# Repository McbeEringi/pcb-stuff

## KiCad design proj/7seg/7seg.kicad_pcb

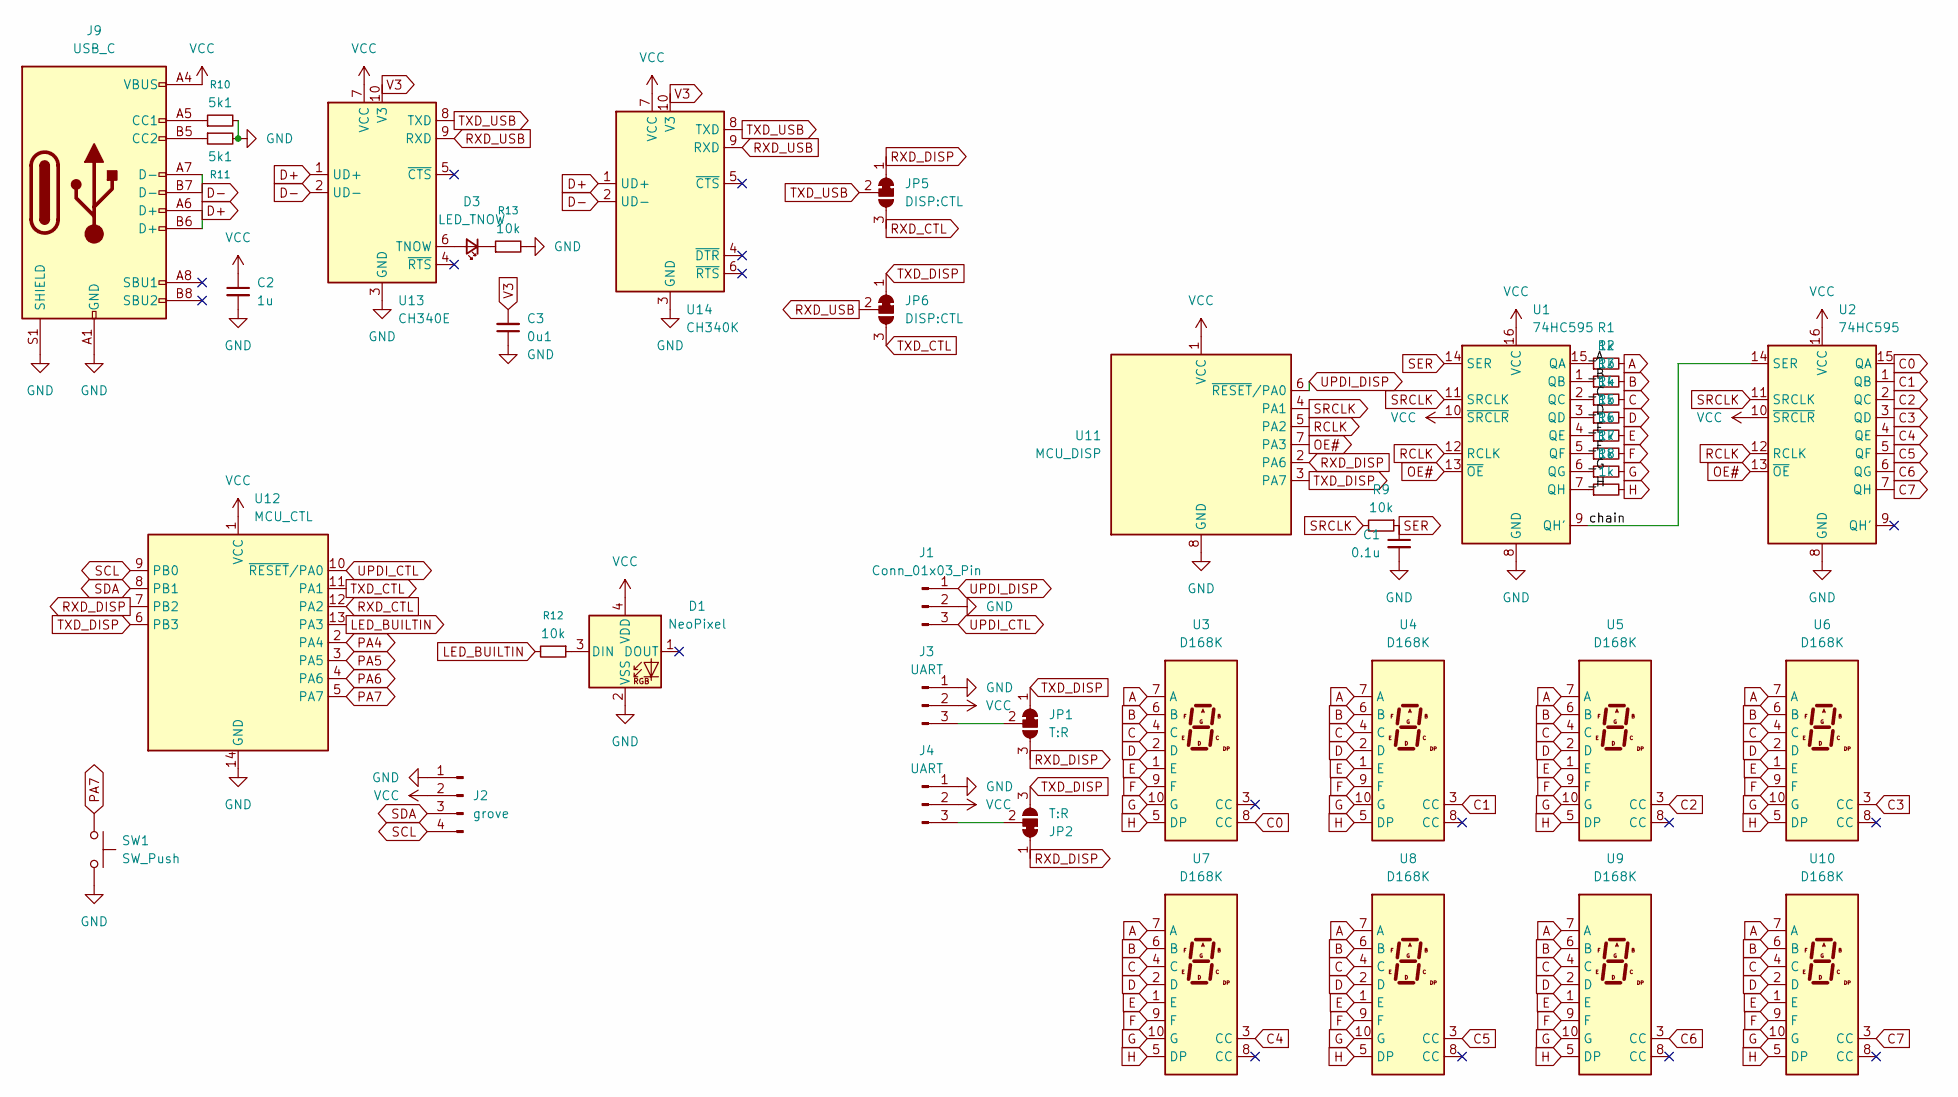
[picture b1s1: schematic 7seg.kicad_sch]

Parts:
C1: 0.1u; C_0603_1608Metric
C2: 1u; C_0603_1608Metric
C3: 0u1; C_0603_1608Metric
D1: NeoPixel; LED_WS2812B-2020_PLCC4_2.0x2.0mm
D3: LED_TNOW; LED_0603_1608Metric
J1: Conn_01x03_Pin; PinHeader_1x03_P2.54mm_Vertical
J2: grove; PinHeader_1x04_P2.54mm_Vertical
J3, J4: UART; PinHeader_1x03_P2.54mm_Vertical
J9: USB_C; USB_C_Receptacle_GCT_USB4105-xx-A_16P_TopMnt_Horizontal
JP1, JP2: T:R; SolderJumper-3_P1.3mm_Bridged12_RoundedPad1.0x1.5mm
JP5, JP6: DISP:CTL; SolderJumper-3_P1.3mm_Bridged12_RoundedPad1.0x1.5mm
R1, R2, R3, R4, R5, R6, R7, R8: 1k; R_0603_1608Metric
R9, R12, R13: 10k; R_0603_1608Metric
R10, R11: 5k1; R_0603_1608Metric
SW1: SW_Push; alps-skrp
U1, U2: 74HC595; TSSOP-16_4.4x5mm_P0.65mm
U3, U4, U5, U6, U7, U8, U9, U10: D168K; D1X8K
U11: MCU_DISP; SOIC-8_3.9x4.9mm_P1.27mm
U12: MCU_CTL; SOIC-14_3.9x8.7mm_P1.27mm
U13: CH340E; MSOP-10_3x3mm_P0.5mm
U14: CH340K; SSOP-10-1EP_3.9x4.9mm_P1mm_EP2.1x3.3mm

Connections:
/_A: R1.1, U1.15 (QA)
/_B: R2.1, U1.1 (QB)
/_C: R3.1, U1.2 (QC)
/_D: R4.1, U1.3 (QD)
/_E: R5.1, U1.4 (QE)
/_F: R6.1, U1.5 (QF)
/_G: R7.1, U1.6 (QG)
/_H: R8.1, U1.7 (QH)
/chain: U1.9 (QH'), U2.14 (SER)
A: R1.2, U3.7 (A), U4.7 (A), U5.7 (A), U6.7 (A), U7.7 (A), U8.7 (A), U9.7 (A), U10.7 (A)
B: R2.2, U3.6 (B), U4.6 (B), U5.6 (B), U6.6 (B), U7.6 (B), U8.6 (B), U9.6 (B), U10.6 (B)
C: R3.2, U3.4 (C), U4.4 (C), U5.4 (C), U6.4 (C), U7.4 (C), U8.4 (C), U9.4 (C), U10.4 (C)
C0: U2.15 (QA), U3.8 (CC)
C1: U2.1 (QB), U4.3 (CC)
C2: U2.2 (QC), U5.3 (CC)
C3: U2.3 (QD), U6.3 (CC)
C4: U2.4 (QE), U7.3 (CC)
C5: U2.5 (QF), U8.3 (CC)
C6: U2.6 (QG), U9.3 (CC)
C7: U2.7 (QH), U10.3 (CC)
D: R4.2, U3.2 (D), U4.2 (D), U5.2 (D), U6.2 (D), U7.2 (D), U8.2 (D), U9.2 (D), U10.2 (D)
D+: J9.A6 (D+), J9.B6 (D+), U13.1 (UD+), U14.1 (UD+)
D-: J9.A7 (D-), J9.B7 (D-), U13.2 (UD-), U14.2 (UD-)
E: R5.2, U3.1 (E), U4.1 (E), U5.1 (E), U6.1 (E), U7.1 (E), U8.1 (E), U9.1 (E), U10.1 (E)
F: R6.2, U3.9 (F), U4.9 (F), U5.9 (F), U6.9 (F), U7.9 (F), U8.9 (F), U9.9 (F), U10.9 (F)
G: R7.2, U3.10 (G), U4.10 (G), U5.10 (G), U6.10 (G), U7.10 (G), U8.10 (G), U9.10 (G), U10.10 (G)
GND: C1.2, C2.2, C3.1, D1.2 (VSS), J1.2, J2.1, J3.1, J4.1, J9.A1 (GND), J9.A12 (GND), J9.B1 (GND), J9.B12 (GND), J9.S1 (SHIELD), R10.2, R11.2, R13.2, SW1.2, U1.8 (GND), U2.8 (GND), U11.8 (GND), U12.14 (GND), U13.3 (GND), U14.3 (GND)
H: R8.2, U3.5 (DP), U4.5 (DP), U5.5 (DP), U6.5 (DP), U7.5 (DP), U8.5 (DP), U9.5 (DP), U10.5 (DP)
LED_BUILTIN: R12.2, U12.13 (PA3)
unnamed: D1.3 (DIN), R12.1
unnamed: D3.2 (A), U13.6 (TNOW)
unnamed: D3.1 (K), R13.1
unnamed: J3.3, JP1.2 (C)
unnamed: J4.3, JP2.2 (C)
unnamed: J9.A5 (CC1), R10.1
unnamed: J9.B5 (CC2), R11.1
OE#: U1.13 (~OE), U2.13 (~OE), U11.7 (PA3)
PA4: U12.2 (PA4)
PA5: U12.3 (PA5)
PA6: U12.4 (PA6)
PA7: SW1.1, U12.5 (PA7)
RCLK: U1.12 (RCLK), U2.12 (RCLK), U11.5 (PA2)
RXD_CTL: JP5.3 (B), U12.12 (PA2)
RXD_DISP: JP1.3 (B), JP2.1 (A), JP5.1 (A), U11.2 (PA6), U12.7 (PB2)
RXD_USB: JP6.2 (C), U13.9 (RXD), U14.9 (RXD)
SCL: J2.4, U12.9 (PB0)
SDA: J2.3, U12.8 (PB1)
SER: C1.1, R9.1, U1.14 (SER)
SRCLK: R9.2, U1.11 (SRCLK), U2.11 (SRCLK), U11.4 (PA1)
TXD_CTL: JP6.3 (B), U12.11 (PA1)
TXD_DISP: JP1.1 (A), JP2.3 (B), JP6.1 (A), U11.3 (PA7), U12.6 (PB3)
TXD_USB: JP5.2 (C), U13.8 (TXD), U14.8 (TXD)
UPDI_CTL: J1.3, U12.10 (~RESET/PA0)
UPDI_DISP: J1.1, U11.6 (~RESET/PA0)
V3: C3.2, U13.10 (V3), U14.10 (V3)
VCC: C2.1, D1.4 (VDD), J2.2, J3.2, J4.2, J9.A4 (VBUS), J9.A9 (VBUS), J9.B4 (VBUS), J9.B9 (VBUS), U1.10 (~SRCLR), U1.16 (VCC), U2.10 (~SRCLR), U2.16 (VCC), U11.1 (VCC), U12.1 (VCC), U13.7 (VCC), U14.7 (VCC)

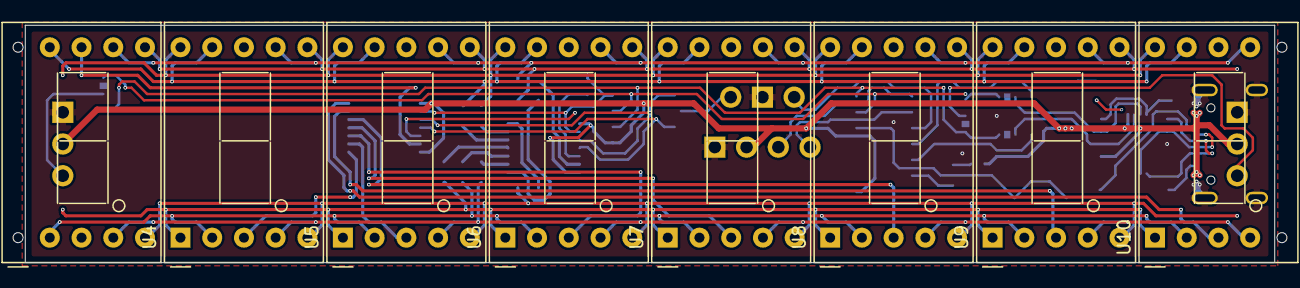
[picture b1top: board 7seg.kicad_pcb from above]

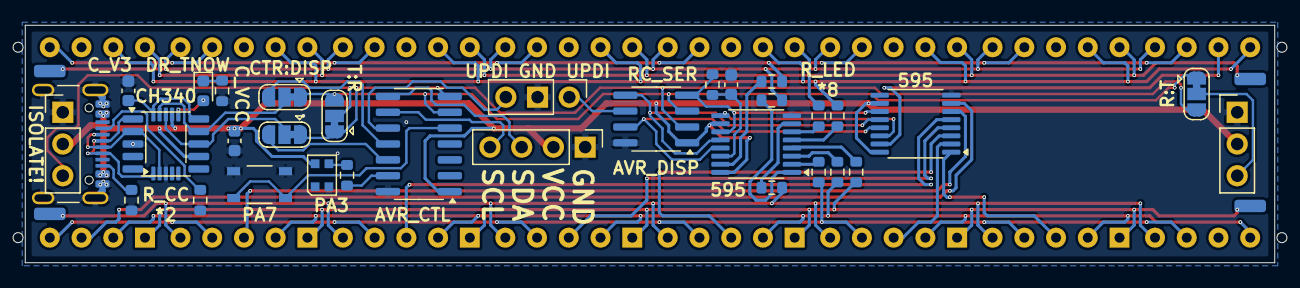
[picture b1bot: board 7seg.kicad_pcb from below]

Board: 2 copper layers, 100.0 x 19.0 mm, 42 parts (34 on the bottom side), 53 nets.

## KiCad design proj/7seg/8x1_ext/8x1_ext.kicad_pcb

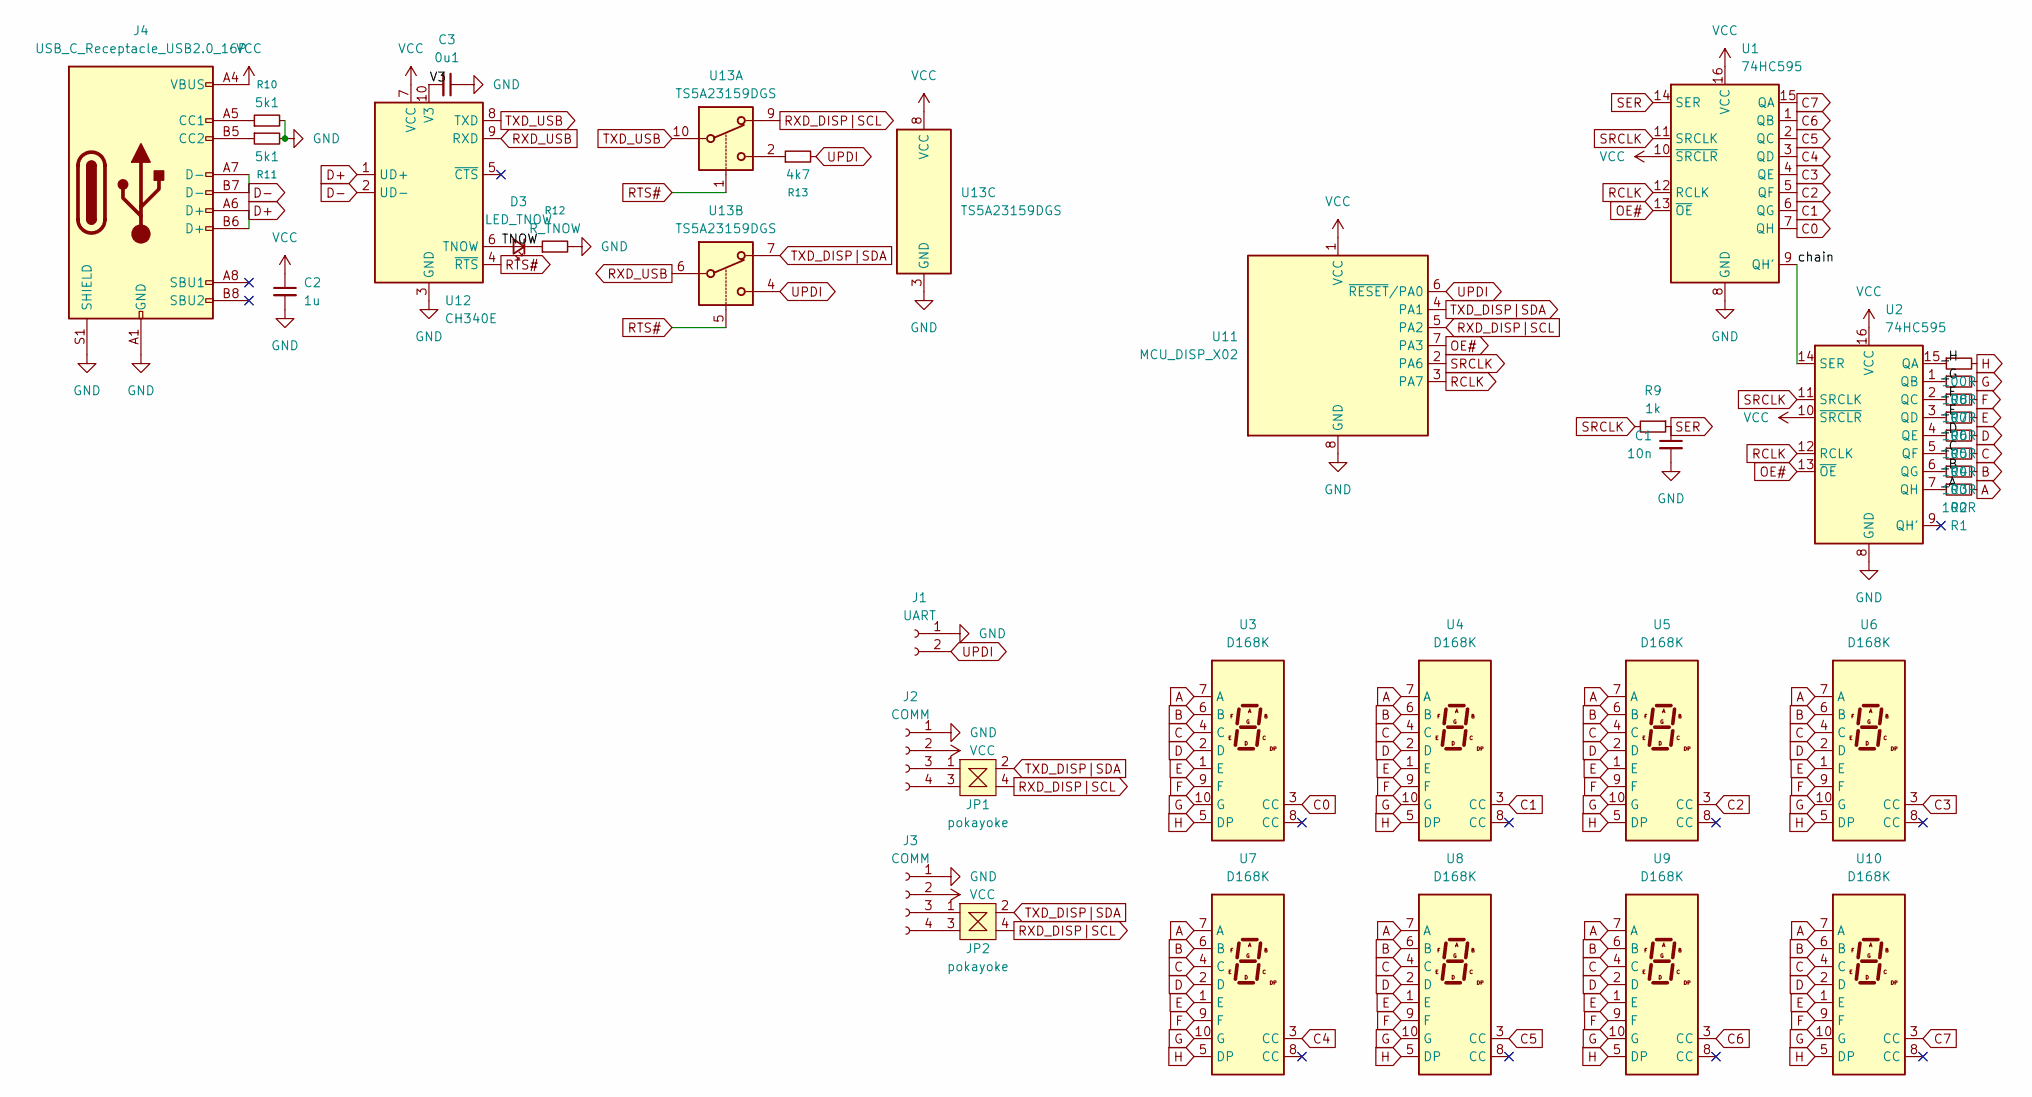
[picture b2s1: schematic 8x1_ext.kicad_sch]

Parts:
C1: 10n; C_0603_1608Metric
C2: 1u; C_0603_1608Metric
C3: 0u1; C_0603_1608Metric
D3: LED_TNOW; LED_0603_1608Metric
J1: UART; PinSocket_1x02_P2.54mm_Vertical
J2, J3: COMM; JST_ZH_B4B-ZR_1x04_P1.50mm_Vertical
J4: USB_C_Receptacle_USB2.0_16P; USB_C_Receptacle_GCT_USB4105-xx-A_16P_TopMnt_Horizontal
JP1, JP2: pokayoke; pokayoke_1608
R1, R2, R3, R4, R5, R6, R7, R8: 100R; R_0603_1608Metric
R9: 1k; R_0603_1608Metric
R10, R11: 5k1; R_0603_1608Metric
R12: R_TNOW; R_0603_1608Metric
R13: 4k7; R_0603_1608Metric
U1, U2: 74HC595; TSSOP-16_4.4x5mm_P0.65mm
U3, U4, U5, U6, U7, U8, U9, U10: D168K; D1X8K
U11: MCU_DISP_X02; SOIC-8_3.9x4.9mm_P1.27mm
U12: CH340E; MSOP-10_3x3mm_P0.5mm
U13: TS5A23159DGS; VSSOP-10_3x3mm_P0.5mm

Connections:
/TNOW: D3.2 (A), U12.6 (TNOW)
/V3: C3.2, U12.10 (V3)
/_A: R1.1, U2.7 (QH)
/_B: R2.1, U2.6 (QG)
/_C: R3.1, U2.5 (QF)
/_D: R4.1, U2.4 (QE)
/_E: R5.1, U2.3 (QD)
/_F: R6.1, U2.2 (QC)
/_G: R7.1, U2.1 (QB)
/_H: R8.1, U2.15 (QA)
/chain: U1.9 (QH'), U2.14 (SER)
A: R1.2, U3.7 (A), U4.7 (A), U5.7 (A), U6.7 (A), U7.7 (A), U8.7 (A), U9.7 (A), U10.7 (A)
B: R2.2, U3.6 (B), U4.6 (B), U5.6 (B), U6.6 (B), U7.6 (B), U8.6 (B), U9.6 (B), U10.6 (B)
C: R3.2, U3.4 (C), U4.4 (C), U5.4 (C), U6.4 (C), U7.4 (C), U8.4 (C), U9.4 (C), U10.4 (C)
C0: U1.7 (QH), U3.3 (CC)
C1: U1.6 (QG), U4.3 (CC)
C2: U1.5 (QF), U5.3 (CC)
C3: U1.4 (QE), U6.3 (CC)
C4: U1.3 (QD), U7.3 (CC)
C5: U1.2 (QC), U8.3 (CC)
C6: U1.1 (QB), U9.3 (CC)
C7: U1.15 (QA), U10.3 (CC)
D: R4.2, U3.2 (D), U4.2 (D), U5.2 (D), U6.2 (D), U7.2 (D), U8.2 (D), U9.2 (D), U10.2 (D)
D+: J4.A6 (D+), J4.B6 (D+), U12.1 (UD+)
D-: J4.A7 (D-), J4.B7 (D-), U12.2 (UD-)
E: R5.2, U3.1 (E), U4.1 (E), U5.1 (E), U6.1 (E), U7.1 (E), U8.1 (E), U9.1 (E), U10.1 (E)
F: R6.2, U3.9 (F), U4.9 (F), U5.9 (F), U6.9 (F), U7.9 (F), U8.9 (F), U9.9 (F), U10.9 (F)
G: R7.2, U3.10 (G), U4.10 (G), U5.10 (G), U6.10 (G), U7.10 (G), U8.10 (G), U9.10 (G), U10.10 (G)
GND: C1.2, C2.2, C3.1, J1.1, J2.1, J3.1, J4.A1 (GND), J4.A12 (GND), J4.B1 (GND), J4.B12 (GND), J4.S1 (SHIELD), R10.2, R11.2, R12.2, U1.8 (GND), U2.8 (GND), U11.8 (GND), U12.3 (GND), U13.3 (GND)
H: R8.2, U3.5 (DP), U4.5 (DP), U5.5 (DP), U6.5 (DP), U7.5 (DP), U8.5 (DP), U9.5 (DP), U10.5 (DP)
unnamed: D3.1 (K), R12.1
unnamed: J2.3, JP1.1
unnamed: J2.4, JP1.3
unnamed: J3.3, JP2.1
unnamed: J3.4, JP2.3
unnamed: J4.A5 (CC1), R10.1
unnamed: J4.B5 (CC2), R11.1
unnamed: R13.1, U13.2
OE#: U1.13 (~OE), U2.13 (~OE), U11.7 (PA3)
RCLK: U1.12 (RCLK), U2.12 (RCLK), U11.3 (PA7)
RTS#: U12.4 (~RTS), U13.1, U13.5
RXD_DISP|SCL: JP1.4, JP2.4, U11.5 (PA2), U13.9
RXD_USB: U12.9 (RXD), U13.6
SER: C1.1, R9.1, U1.14 (SER)
SRCLK: R9.2, U1.11 (SRCLK), U2.11 (SRCLK), U11.2 (PA6)
TXD_DISP|SDA: JP1.2, JP2.2, U11.4 (PA1), U13.7
TXD_USB: U12.8 (TXD), U13.10
UPDI: J1.2, R13.2, U11.6 (~RESET/PA0), U13.4
VCC: C2.1, J2.2, J3.2, J4.A4 (VBUS), J4.A9 (VBUS), J4.B4 (VBUS), J4.B9 (VBUS), U1.10 (~SRCLR), U1.16 (VCC), U2.10 (~SRCLR), U2.16 (VCC), U11.1 (VCC), U12.7 (VCC), U13.8 (VCC)

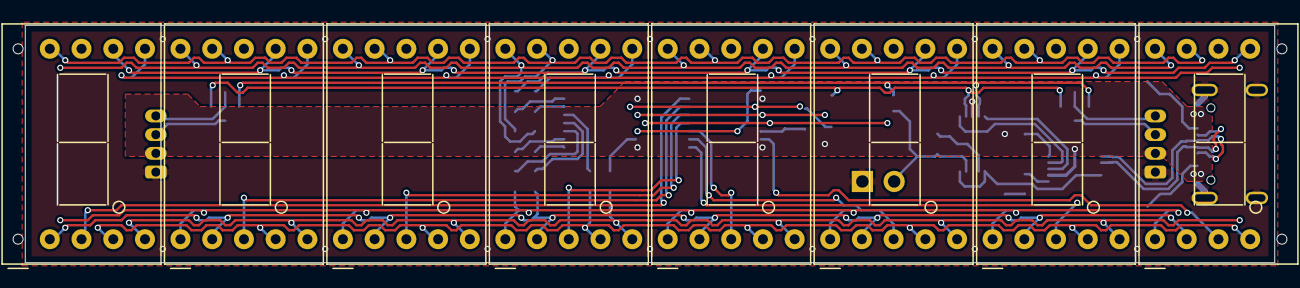
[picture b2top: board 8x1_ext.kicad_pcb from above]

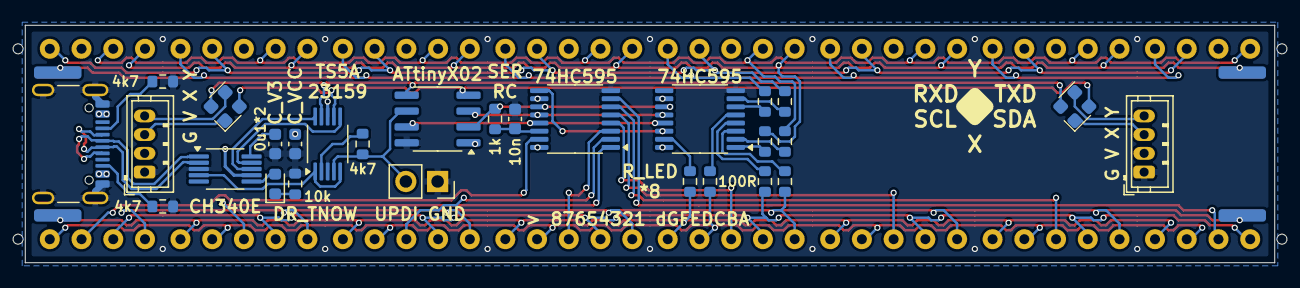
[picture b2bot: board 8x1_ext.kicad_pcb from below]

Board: 2 copper layers, 100.0 x 19.0 mm, 36 parts (28 on the bottom side), 49 nets.

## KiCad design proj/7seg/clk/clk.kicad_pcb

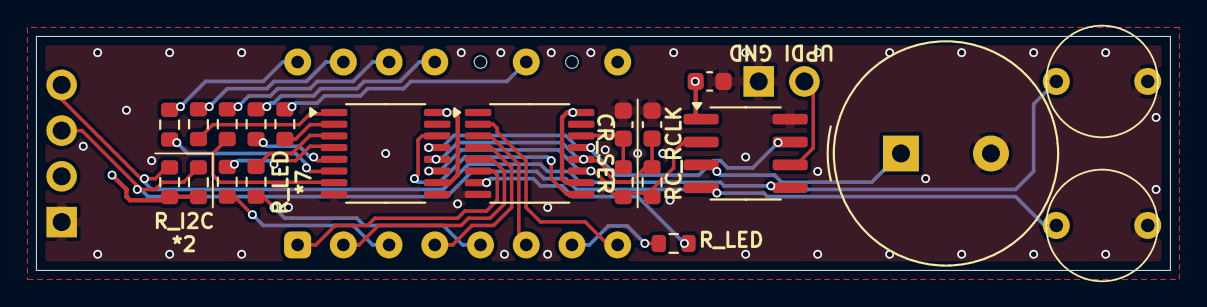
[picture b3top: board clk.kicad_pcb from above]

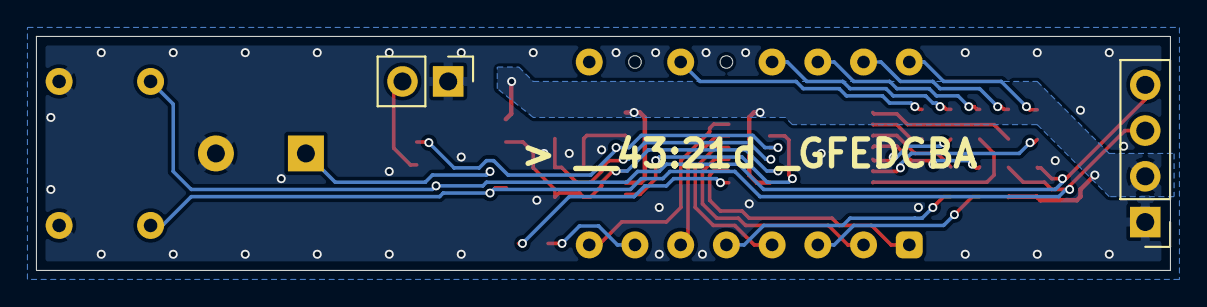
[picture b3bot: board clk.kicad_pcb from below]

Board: 2 copper layers, 63.0 x 13.0 mm, 24 parts (2 on the bottom side), 32 nets.

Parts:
BZ1: Buzzer; Buzzer_TDK_PS1240P02BT_D12.2mm_H6.5mm
C1: C_RCLK; C_0603_1608Metric
C2: C_SER; C_0603_1608Metric
C3: 1u; C_0603_1608Metric
J1: Conn_01x02_Pin; PinHeader_1x02_P2.54mm_Vertical
J2: Conn_01x04_Pin; PinHeader_1x04_P2.54mm_Vertical
R1, R2, R3, R4, R5, R6, R7, R8: 1k; R_0603_1608Metric
R9: R_RCLK; R_0603_1608Metric
R10: R_SER; R_0603_1608Metric
R11, R12: R_I2C; R_0603_1608Metric
SW1, SW2: SW_Push; alps-skrg
U1: LTC-4627JG; LTC-4627Jx
U2, U3: 74HC595; TSSOP-16_4.4x5mm_P0.65mm
U4: ATtiny402-SS; SOIC-8_3.9x4.9mm_P1.27mm

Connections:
/_SEG1: R1.1, U2.7 (QH)
/_SEG2: R2.1, U2.6 (QG)
/_SEG3: R3.1, U2.5 (QF)
/_SEG4: R4.1, U2.4 (QE)
/_SEG5: R5.1, U2.3 (QD)
/_SEG6: R6.1, U2.2 (QC)
/_SEG7: R7.1, U2.1 (QB)
/_SEG8: R8.1, U3.7 (QH)
GND: BZ1.2 (-), C1.2, C2.2, C3.2, J1.1, J2.1, SW1.2, SW2.2, U2.8 (GND), U3.8 (GND), U4.8 (GND)
OE#: U2.13 (~OE), U3.13 (~OE), U4.7 (PA3)
PA1: J2.3, R11.2, SW1.1, U4.4 (PA1)
PA2: J2.4, R12.2, SW2.1, U4.5 (PA2)
RCLK: C1.1, R9.2, U2.12 (RCLK), U3.12 (RCLK)
SEG1: R1.2, U1.14 (A)
SEG2: R2.2, U1.16 (B)
SEG3: R3.2, U1.13 (C)
SEG4: R4.2, U1.3 (D)
SEG5: R5.2, U1.5 (E)
SEG6: R6.2, U1.11 (F)
SEG7: R7.2, U1.15 (G)
SEG8: R8.2, U1.7 (DP)
SEGC1: U1.1 (CA1), U3.6 (QG)
SEGC2: U1.2 (CA2), U3.5 (QF)
SEGC3: U1.6 (CA3), U3.3 (QD)
SEGC4: U1.8 (CA4), U3.2 (QC)
SEGC:: U1.4 (CAL), U3.4 (QE)
SER: C2.1, R10.2, U3.14 (SER)
SPK: BZ1.1 (+), U4.3 (PA7)
SRCLK: R9.1, R10.1, U2.11 (SRCLK), U3.11 (SRCLK), U4.2 (PA6)
UPDI: J1.2, U4.6 (~RESET/PA0)
VCC: C3.1, J2.2, R11.1, R12.1, U2.10 (~SRCLR), U2.16 (VCC), U3.10 (~SRCLR), U3.16 (VCC), U4.1 (VCC)
chain: U2.14 (SER), U3.9 (QH')

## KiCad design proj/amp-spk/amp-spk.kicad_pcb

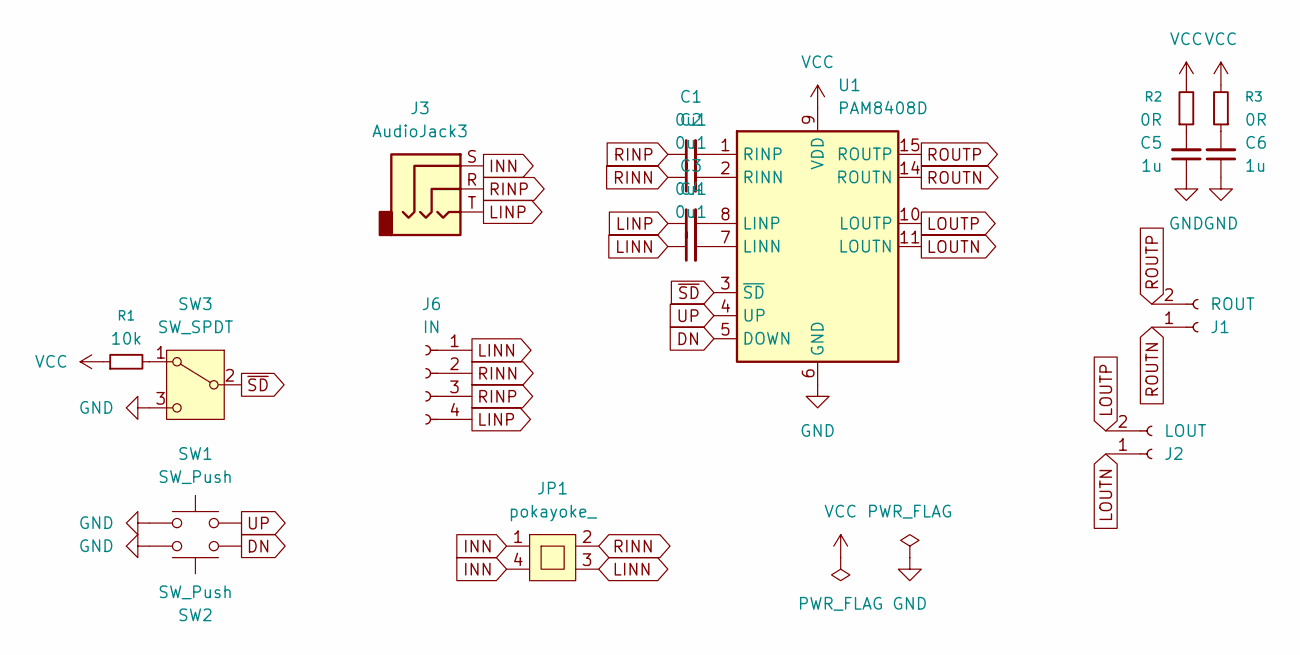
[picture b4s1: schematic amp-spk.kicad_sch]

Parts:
C1, C2, C3, C4: 0u1; C_0603_1608Metric
C5, C6: 1u; C_0603_1608Metric
J1: ROUT; JST_XH_B2B-XH-A_1x02_P2.50mm_Vertical
J2: LOUT; JST_XH_B2B-XH-A_1x02_P2.50mm_Vertical
J3: AudioJack3; MJ-8435
J6: IN; JST_ZH_B4B-ZR_1x04_P1.50mm_Vertical
JP1: pokayoke_; pokayoke_1608
R1: 10k; R_0603_1608Metric
R2, R3: 0R; R_0603_1608Metric
SW1, SW2: SW_Push; alps-skrg
SW3: SW_SPDT; sw
U1: PAM8408D; SOP-16_3.9x9.9mm_P1.27mm

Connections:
DN: SW2.2, U1.5 (DOWN)
GND: C5.1, C6.1, SW1.1, SW2.1, SW3.3 (C), U1.6 (GND), U1.12 (GND), U1.13 (GND)
INN: J3.S, JP1.1, JP1.4
LINN: C4.1, J6.1, JP1.3
LINP: C3.1, J3.T, J6.4
LOUTN: J2.1, U1.11 (LOUTN)
LOUTP: J2.2, U1.10 (LOUTP)
unnamed: C5.2, R2.1
unnamed: C6.2, R3.1
unnamed: R1.2, SW3.1 (A)
unnamed: C4.2, U1.7 (LINN)
unnamed: C3.2, U1.8 (LINP)
unnamed: C2.2, U1.2 (RINN)
unnamed: C1.2, U1.1 (RINP)
RINN: C2.1, J6.2, JP1.2
RINP: C1.1, J3.R, J6.3
ROUTN: J1.1, U1.14 (ROUTN)
ROUTP: J1.2, U1.15 (ROUTP)
UP: SW1.2, U1.4 (UP)
VCC: R1.1, R2.2, R3.2, U1.9 (VDD), U1.16 (VDD)
~SD: SW3.2 (B), U1.3 (~SD)

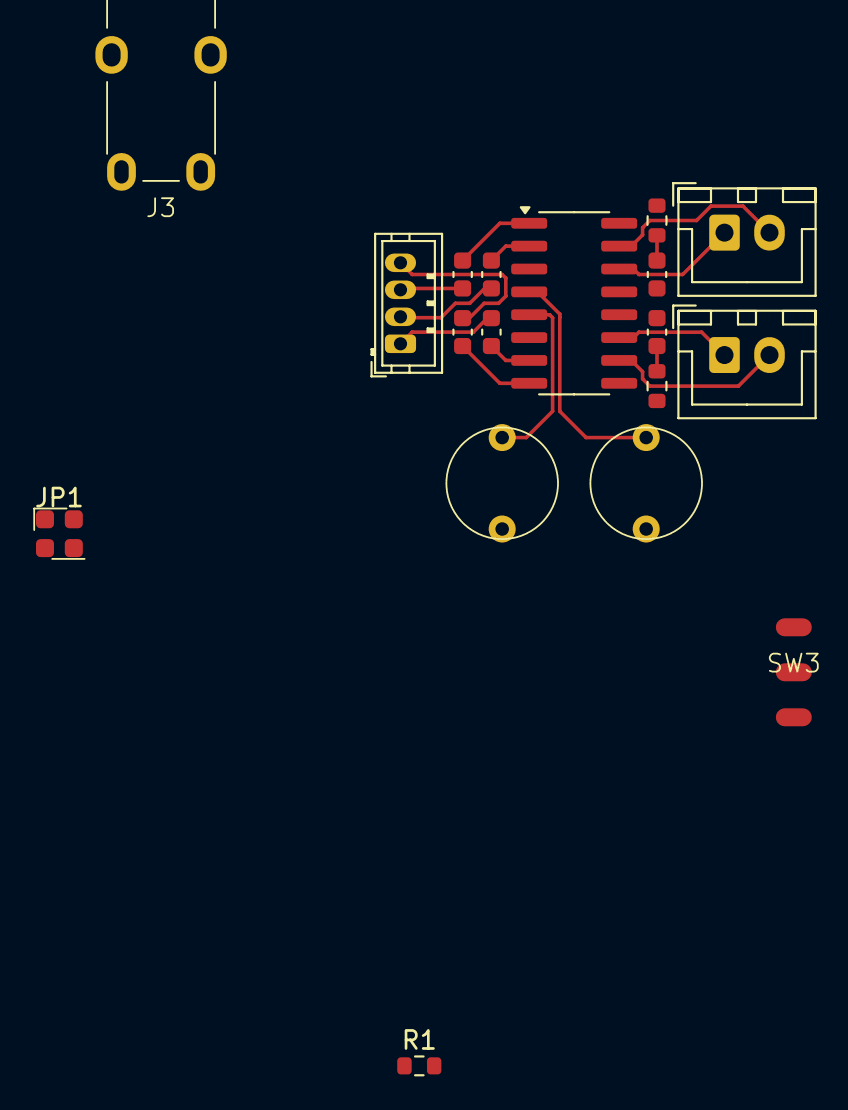
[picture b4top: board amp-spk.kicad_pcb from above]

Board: 2 copper layers, 18 parts (0 on the bottom side), 21 nets.

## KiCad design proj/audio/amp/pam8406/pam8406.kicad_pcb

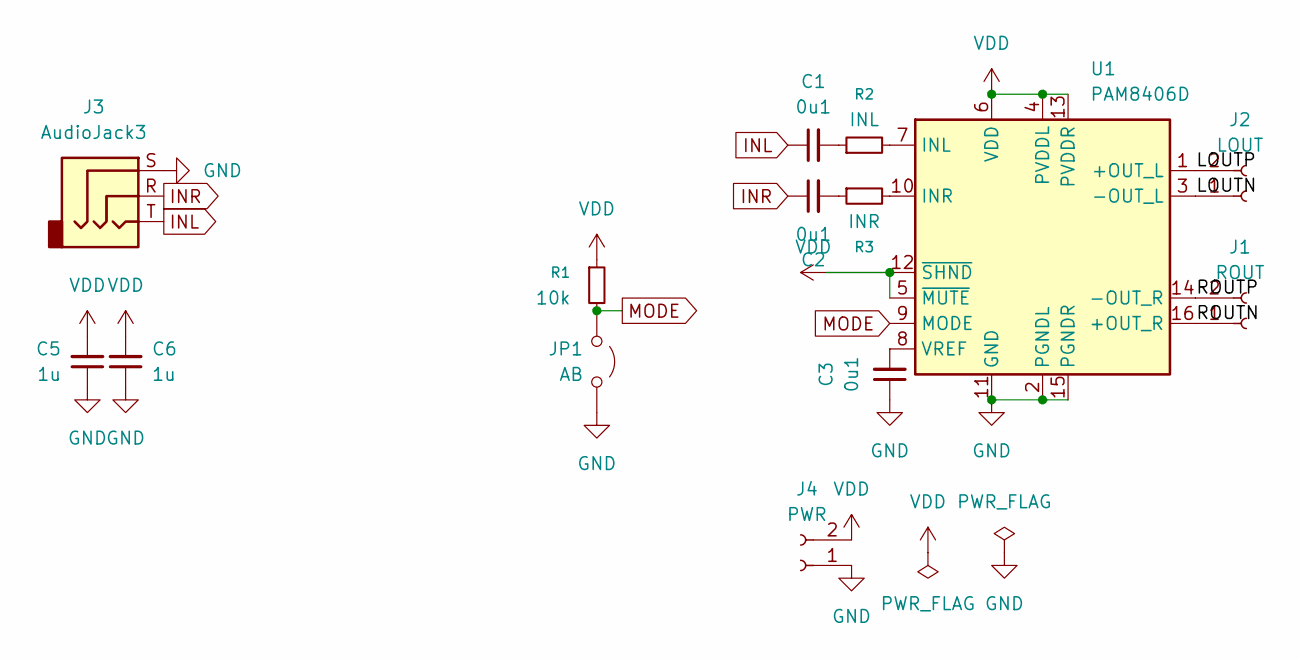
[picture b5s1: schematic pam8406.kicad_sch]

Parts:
C1, C2, C3: 0u1; C_0603_1608Metric
C5, C6: 1u; C_0603_1608Metric
J1: ROUT; JST_XH_S2B-XH-A_1x02_P2.50mm_Horizontal
J2: LOUT; JST_XH_S2B-XH-A_1x02_P2.50mm_Horizontal
J3: AudioJack3; MJ-8435
J4: PWR; JST_XH_S2B-XH-A_1x02_P2.50mm_Horizontal
JP1: AB; PinHeader_1x02_P2.54mm_Vertical
R1: 10k; R_0603_1608Metric
R2: INL; R_0603_1608Metric
R3: INR; R_0603_1608Metric
U1: PAM8406D; SOIC-16_3.9x9.9mm_P1.27mm

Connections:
/LOUTN: J2.1, U1.3 (-OUT_L)
/LOUTP: J2.2, U1.1 (+OUT_L)
/ROUTN: J1.1, U1.16 (+OUT_R)
/ROUTP: J1.2, U1.14 (-OUT_R)
GND: C3.1, C5.1, C6.1, J3.S, J4.1, JP1.1 (A), U1.2 (PGNDL), U1.11 (GND), U1.15 (PGNDR)
INL: C1.1, J3.T
INR: C2.1, J3.R
MODE: JP1.2 (B), R1.2, U1.9 (MODE)
unnamed: C1.2, R2.1
unnamed: C2.2, R3.1
unnamed: R2.2, U1.7 (INL)
unnamed: R3.2, U1.10 (INR)
unnamed: C3.2, U1.8 (VREF)
VDD: C5.2, C6.2, J4.2, R1.1, U1.4 (PVDDL), U1.5 (~MUTE), U1.6 (VDD), U1.12 (~SHND), U1.13 (PVDDR)

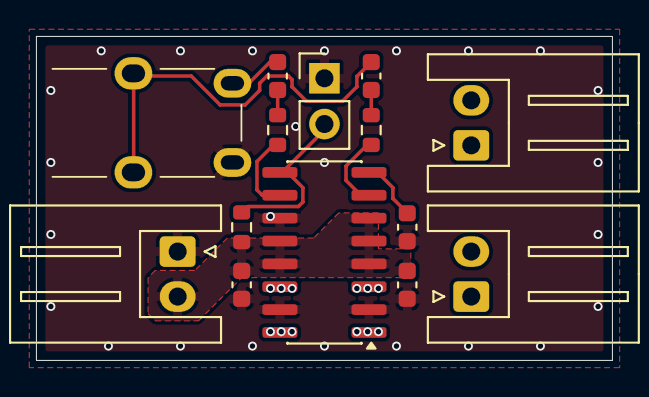
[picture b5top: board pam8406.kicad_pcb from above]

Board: 2 copper layers, 32.0 x 18.0 mm, 14 parts (0 on the bottom side), 14 nets.

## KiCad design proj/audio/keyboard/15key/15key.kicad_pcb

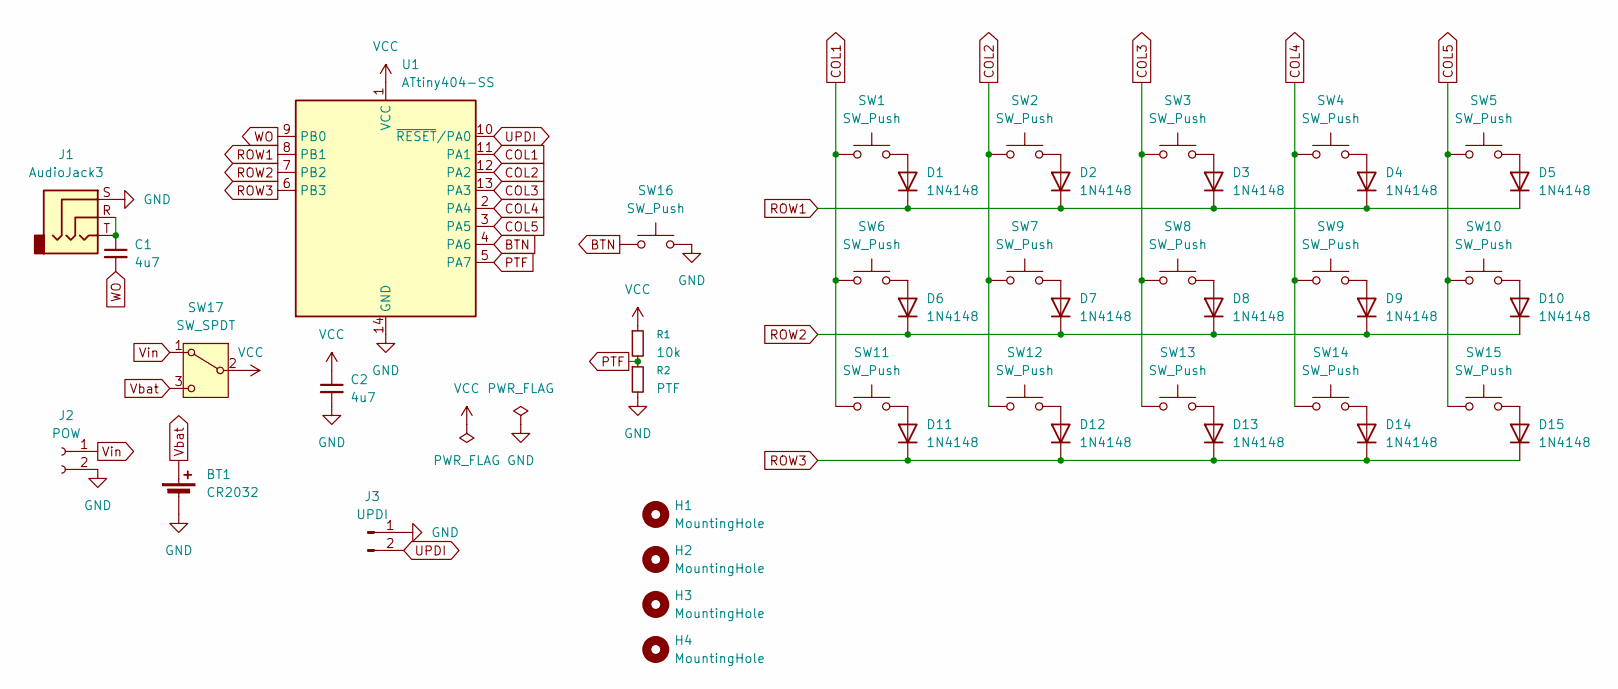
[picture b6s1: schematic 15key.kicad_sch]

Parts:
BT1: CR2032; BatteryHolder_Multicomp_BC-2001_1x2032
C1, C2: 4u7; C_0603_1608Metric
D1, D2, D3, D4, D5, D6, D7, D8, D9, D10, D11, D12, D13, D14, D15: 1N4148; D_DO-35_SOD27_P7.62mm_Horizontal
H1, H2, H3, H4: MountingHole; MountingHole_3.2mm_M3
J1: AudioJack3; MJ-8435
J2: POW; JST_XH_S2B-XH-A_1x02_P2.50mm_Horizontal
J3: UPDI; PinHeader_1x02_P2.54mm_Vertical
R1: 10k; R_0603_1608Metric
R2: PTF; R_1020_2550Metric
SW1, SW2, SW3, SW4, SW5, SW6, SW7, SW8, SW9, SW10, SW11, SW12, SW13, SW14, SW15: SW_Push; SW_Cherry_MX_1.00u_PCB
SW16: SW_Push; alps-skrg
SW17: SW_SPDT; SW_Slide_SPDT_Straight_CK_OS102011MS2Q
U1: ATtiny404-SS; SOIC-14_3.9x8.7mm_P1.27mm

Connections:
BTN: SW16.1, U1.4 (PA6)
COL1: SW1.1, SW6.1, SW11.1, U1.11 (PA1)
COL2: SW2.1, SW7.1, SW12.1, U1.12 (PA2)
COL3: SW3.1, SW8.1, SW13.1, U1.13 (PA3)
COL4: SW4.1, SW9.1, SW14.1, U1.2 (PA4)
COL5: SW5.1, SW10.1, SW15.1, U1.3 (PA5)
GND: BT1.2 (-), C2.2, J1.S, J2.2, J3.1, R2.2, SW16.2, U1.14 (GND)
unnamed: C1.1, J1.R, J1.T
unnamed: D1.2 (A), SW1.2
unnamed: D2.2 (A), SW2.2
unnamed: D3.2 (A), SW3.2
unnamed: D4.2 (A), SW4.2
unnamed: D5.2 (A), SW5.2
unnamed: D6.2 (A), SW6.2
unnamed: D7.2 (A), SW7.2
unnamed: D8.2 (A), SW8.2
unnamed: D9.2 (A), SW9.2
unnamed: D10.2 (A), SW10.2
unnamed: D11.2 (A), SW11.2
unnamed: D12.2 (A), SW12.2
unnamed: D13.2 (A), SW13.2
unnamed: D14.2 (A), SW14.2
unnamed: D15.2 (A), SW15.2
PTF: R1.2, R2.1, U1.5 (PA7)
ROW1: D1.1 (K), D2.1 (K), D3.1 (K), D4.1 (K), D5.1 (K), U1.8 (PB1)
ROW2: D6.1 (K), D7.1 (K), D8.1 (K), D9.1 (K), D10.1 (K), U1.7 (PB2)
ROW3: D11.1 (K), D12.1 (K), D13.1 (K), D14.1 (K), D15.1 (K), U1.6 (PB3)
UPDI: J3.2, U1.10 (~RESET/PA0)
VCC: C2.1, R1.1, SW17.2 (B), U1.1 (VCC)
Vbat: BT1.1 (+), SW17.3 (C)
Vin: J2.1, SW17.1 (A)
WO: C1.2, U1.9 (PB0)

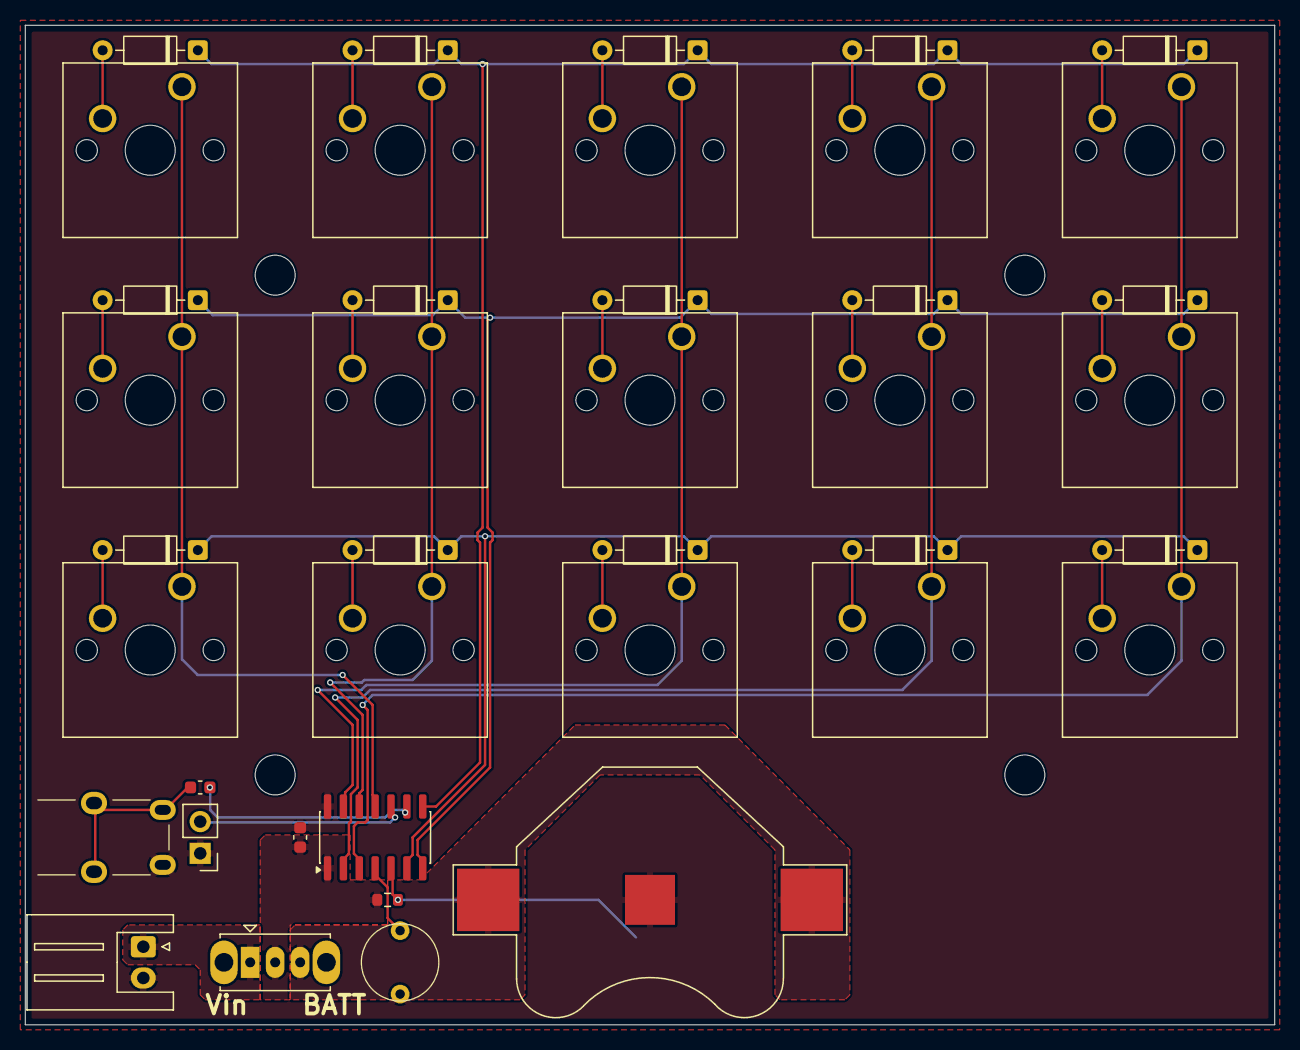
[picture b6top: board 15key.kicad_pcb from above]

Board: 2 copper layers, 100.0 x 80.0 mm, 45 parts (1 on the bottom side), 32 nets.
